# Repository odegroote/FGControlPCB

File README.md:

# FGControlPCB

A PCB for a two channel functiongenerator based on the AD9833 
with adjustable peak voltage to a maximum of 10 Volts and
adjustable offset. It was designed using KiCAD v9.0.

Trying vertical layout for opamps

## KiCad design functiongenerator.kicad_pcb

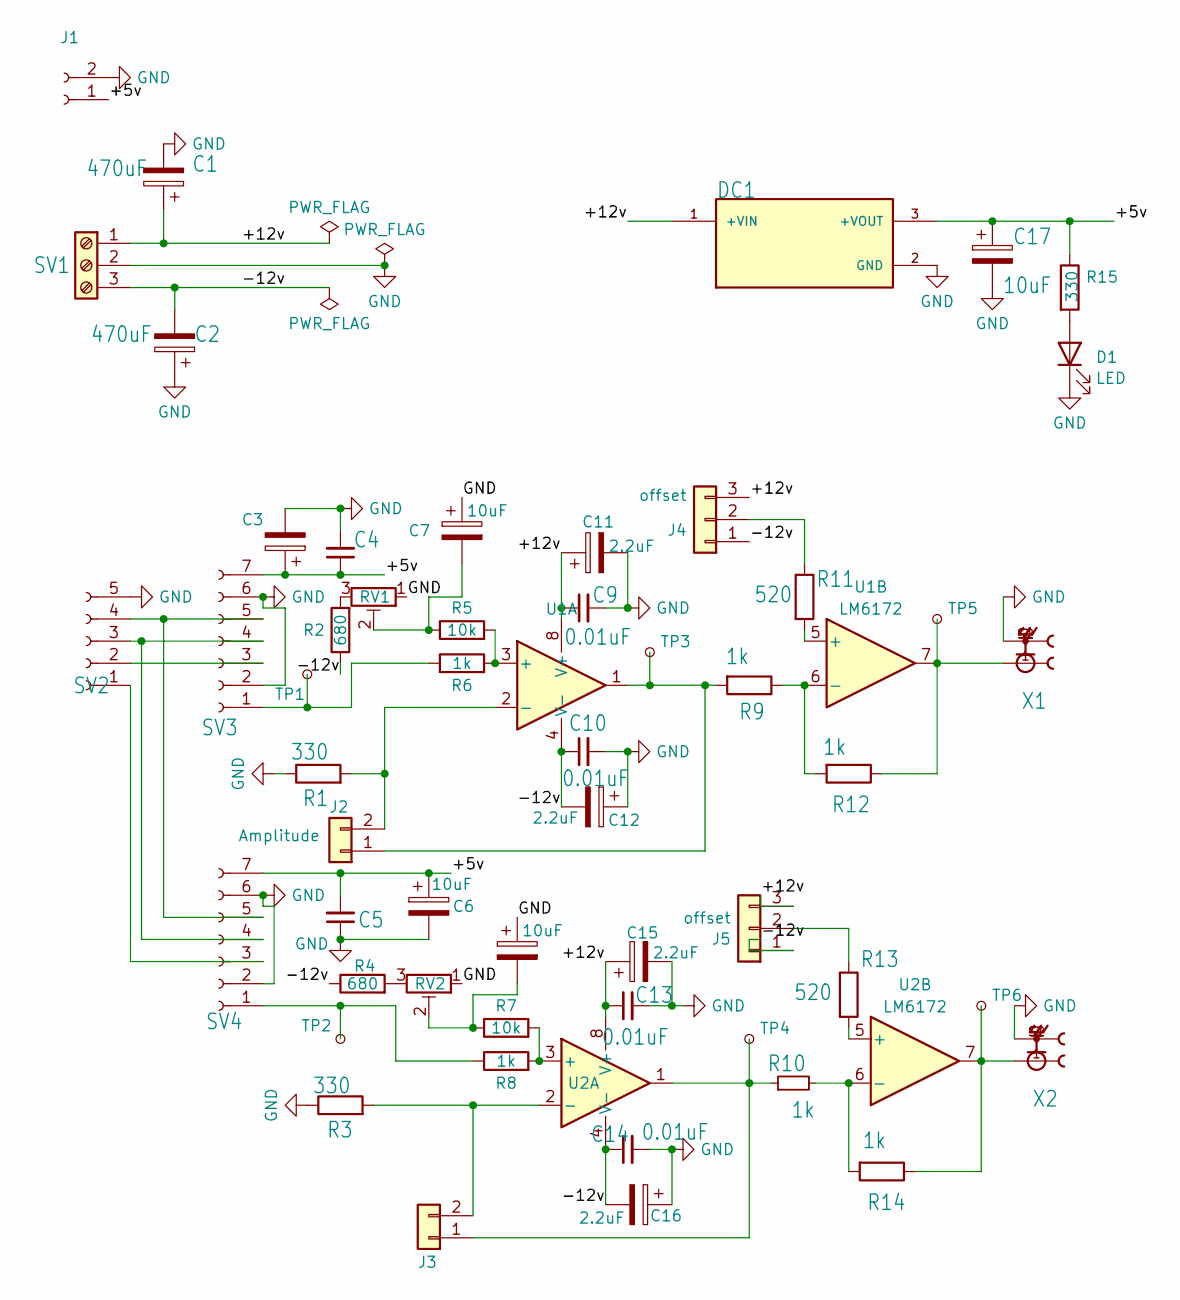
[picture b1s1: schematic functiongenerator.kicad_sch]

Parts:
C1, C2: 470uF; CP_Radial_D12.5mm_P5.00mm
C3, C6, C7, C8: 10uF; CP_Radial_Tantal_D4.5mm_P2.50mm
C4, C5: 100nF; C_Disc_D3.0mm_W1.6mm_P2.50mm
C9, C10, C13, C14: 0.01uF; C_Disc_D3.0mm_W1.6mm_P2.50mm
C11, C12, C15, C16: 2.2uF; CP_Radial_Tantal_D4.5mm_P2.50mm
C17: 10uF; CP_Radial_D12.5mm_P5.00mm
D1: LED; LED_D3.0mm
DC1: Converter_DCDC_TRACO_TSR-1_THT; PARTREV Apr 27, 2020
J1: Conn_01x02_Socket; PinSocket_1x02_P2.54mm_Vertical
J2, J3: Amplitude; JST_XH_B2B-XH-A_1x02_P2.50mm_Vertical
J4, J5: offset; JST_XH_B3B-XH-A_1x03_P2.50mm_Vertical
R1, R3, R15: 330; R_Axial_DIN0207_L6.3mm_D2.5mm_P7.62mm_Horizontal
R2, R4: 680; R_Axial_DIN0207_L6.3mm_D2.5mm_P7.62mm_Horizontal
R5, R7: 10k; R_Axial_DIN0207_L6.3mm_D2.5mm_P7.62mm_Horizontal
R6, R8, R9, R10, R12, R14: 1k; R_Axial_DIN0207_L6.3mm_D2.5mm_P7.62mm_Horizontal
R11, R13: 520; R_Axial_DIN0207_L6.3mm_D2.5mm_P7.62mm_Horizontal
RV1, RV2: 500; Potentiometer_Bourns_3296W_Vertical
SV1: TERM-3; TerminalBlock_Phoenix_PT-1,5-3-3.5-H_1x03_P3.50mm_Horizontal
SV2: Conn_01x05_Socket; PinSocket_1x05_P2.54mm_Vertical
SV3, SV4: Conn_01x07_Socket; PinSocket_1x07_P2.54mm_Vertical
TP1, TP2, TP3, TP4, TP5, TP6: TestPoint_Small; TestPoint_Pad_D1.0mm
U1, U2: LM6172; DIP-8_W7.62mm
X1: CON1; LINX_CONBNC002
X2: CON2; LINX_CONBNC002

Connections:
/+5v: C3.1, C4.1, C5.2, C6.1, C17.1, DC1.3 (+VOUT), J1.1, R15.1, SV3.7, SV4.7
/+12v: C1.1, C9.1, C11.1, C13.1, C15.1, DC1.1 (+VIN), J4.3, J5.3, SV1.1, U1.8 (V+), U2.8 (V+)
/-12v: C2.2, C10.1, C12.2, C14.1, C16.2, J4.1, J5.1, R2.1, R4.1, SV1.3, U1.4 (V-), U2.4 (V-)
GND: C1.2, C2.1, C3.2, C4.2, C5.1, C6.2, C7.1, C8.1, C9.2, C10.2, C11.2, C12.1, C13.2, C14.2, C15.2, C16.1, C17.2, D1.1 (K), DC1.2 (GND), J1.2, R1.1, R3.1, RV1.1, RV2.1, SV1.2, SV2.5, SV3.2, SV3.6, SV4.2, SV4.6, X1.2, X1.S1, X1.S2, X2.2, X2.S1, X2.S2
unnamed: C7.2, R5.1, RV1.2
unnamed: C8.2, R7.1, RV2.2
unnamed: D1.2 (A), R15.2
unnamed: J2.1, R9.2, TP3.1, U1.1
unnamed: J2.2, R1.2, U1.2 (-)
unnamed: J3.1, R10.1, TP4.1, U2.1
unnamed: J3.2, R3.2, U2.2 (-)
unnamed: J4.2, R11.1
unnamed: J5.2, R13.1
unnamed: R2.2, RV1.3
unnamed: R4.2, RV2.3
unnamed: R12.1, TP5.1, U1.7, X1.1
unnamed: R14.1, TP6.1, U2.7, X2.1
unnamed: SV2.1, SV4.3
unnamed: SV2.2, SV3.3
unnamed: SV2.3, SV3.4, SV4.4
unnamed: SV2.4, SV3.5, SV4.5
unnamed: R6.1, SV3.1, TP1.1
unnamed: R8.1, SV4.1, TP2.1
unnamed: R5.2, R6.2, U1.3 (+)
unnamed: R11.2, U1.5 (+)
unnamed: R9.1, R12.2, U1.6 (-)
unnamed: R7.2, R8.2, U2.3 (+)
unnamed: R13.2, U2.5 (+)
unnamed: R10.2, R14.2, U2.6 (-)

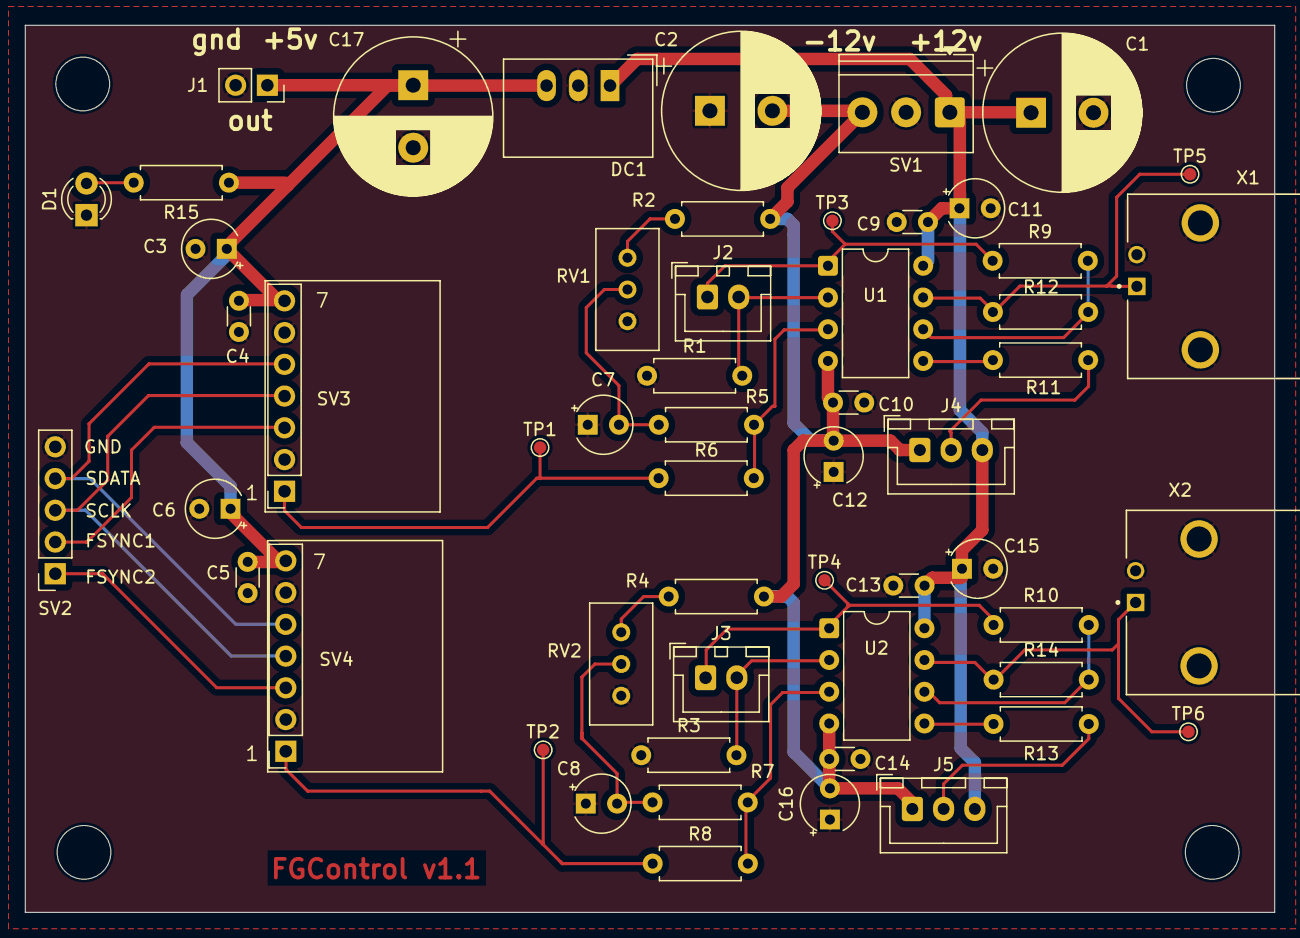
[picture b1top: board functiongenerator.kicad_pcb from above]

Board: 2 copper layers, 100.0 x 71.0 mm, 55 parts (0 on the bottom side), 29 nets.

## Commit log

2025-04-14 updated eradme.md
2025-04-15 switch to vertical layout
2025-04-16 pre release
2025-04-16 pre release v2
2025-04-16 add Tracopower TSR models
2025-04-18 optimized pcb layout
2025-04-19 optimizing pcb design
2025-04-22 added gnd to inout connector to reduce grounding loops
2025-04-27 updated all footprints
2025-04-29 first cleanup groundplane
2025-05-03 moved offset potmeter connections
2025-05-05 removed exces traces
2025-05-09 more sparation between digital tracks channel 1
2025-05-09 attached agnd to common gnd moved +5v connector to board edge
2025-05-10 seperated channels more updated label to v1.1
